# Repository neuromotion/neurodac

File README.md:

# Installation
## Python
The python code relies on the "sounddevice" package. Install this using:
'''pip install sounddevice"
## MATLAB
The MATLAB code relies on the Audio Systems Toolbox. To install it go to the add-on manager in MATLAB IDE,
search for this toolbox and install it. This is not a standard toolbox so you may need to check with your
insitution to make sure you have access to it (I had to get Brown to purchase it). If you cannot get access 
the Python code works just as well.
# Description of files
## eagle-schematic/
Contains the eagle schematics for the NeuroDAC signal conditioning PCB.
## MATLAB/
Contains example code for using NeuroDAC with MATLAB
### playSine.m
This is a script to play 30 seconds of a sine wave a different frequencies on each channel.
This is helpful for testing the system and making sure that you have all the software installed properly.
### playDAC.m
A function for playing a vector of data using a single channel of NeuroDAC
### playDACSimul.m
A function for playing 8 channels of data out of NeuroDAC simultaneously
## Python/
Contains example code for using the NeuroDAC with Python
### playSine.py
This is a Python file that works similarly to the MATLAB_Sine script described above. It plays 8 sine waves each at 10 Hz out of all channels of the NeuroDAC. Use this to test your system.

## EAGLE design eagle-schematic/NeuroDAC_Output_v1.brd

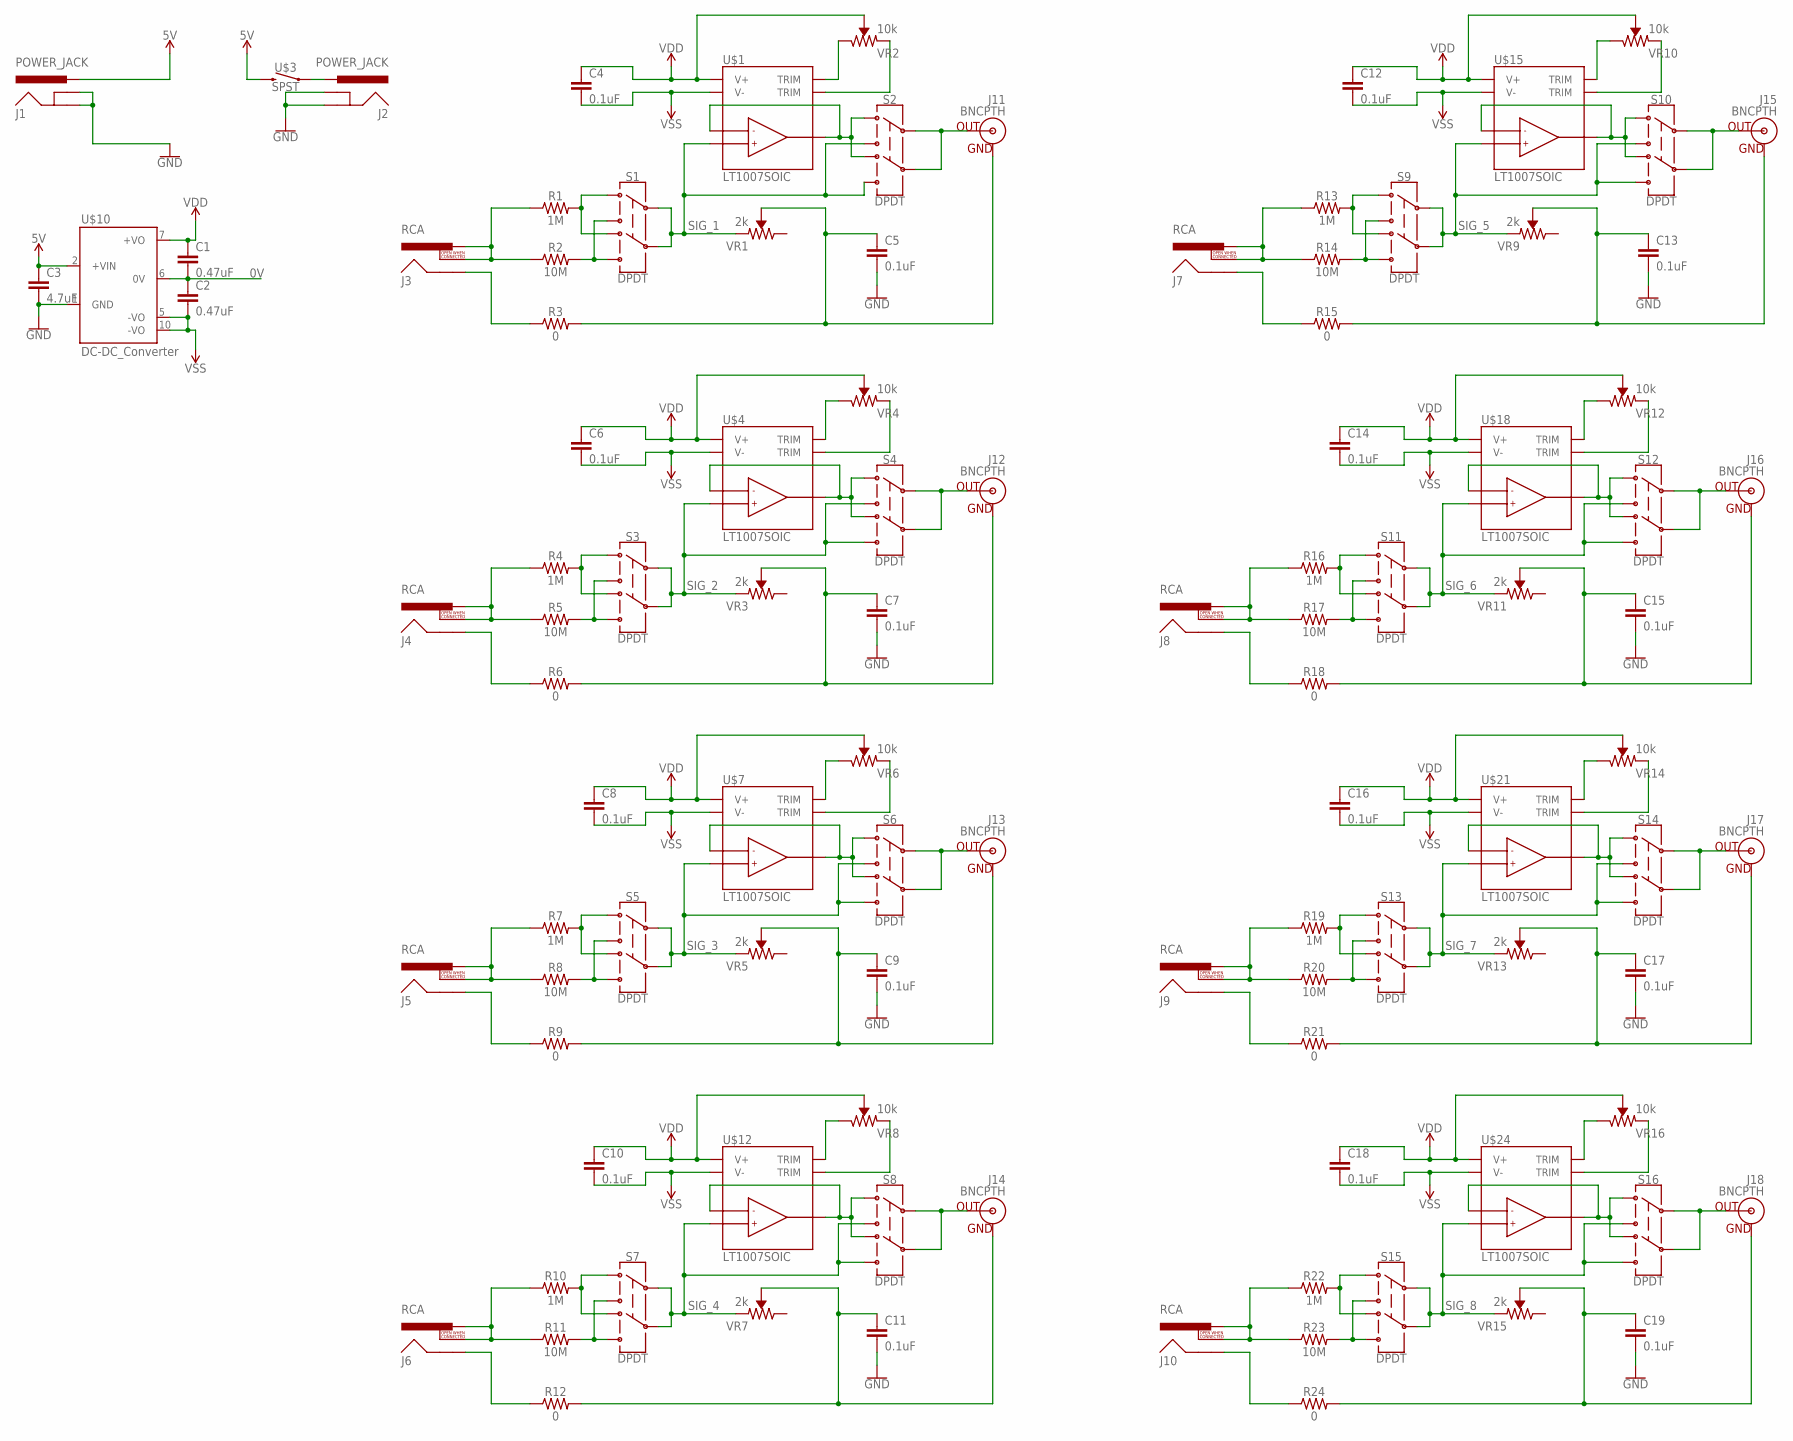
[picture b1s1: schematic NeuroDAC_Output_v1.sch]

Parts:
C1, C2: 0.47uF; 0603
C3: 4.7uF; 0805
C4, C5, C6, C7, C8, C9, C10, C11, C12, C13, C14, C15, C16, C17, C18, C19: 0.1uF; 0603
J1, J2: POWER_JACK; POWER_JACK_PTH
J3, J4, J5, J6, J7, J8, J9, J10: RCA; RCA_LARGE_HOLE
J11, J12, J13, J14, J15, J16, J17, J18: BNCPTH; BNC
R1, R4, R7, R10, R13, R16, R19, R22: 1M; 0603
R2, R5, R8, R11, R14, R17, R20, R23: 10M; 0603
R3, R6, R9, R12, R15, R18, R21, R24: 0; 0603
S1, S2, S3, S4, S5, S6, S7, S8, S9, S10, S11, S12, S13, S14, S15, S16: DPDT; SWITCH_DPDT_JS202011SCQN
U$1, U$4, U$7, U$12, U$15, U$18, U$21, U$24: LT1007SOIC; S8
U$3: SPST; SWITCH_SPST_L101011MS02Q
U$10: DC-DC_Converter; VAT2-SMT
VR1, VR3, VR5, VR7, VR9, VR11, VR13, VR15: 2k; TRIMPOT-SMD-ST4EB
VR2, VR4, VR6, VR8, VR10, VR12, VR14, VR16: 10k; TRIMPOT-SMD-ST4EB

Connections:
0V: C1.2, C2.1, C5.1, C7.1, C9.1, C11.1, C13.1, C15.1, C17.1, C19.1, J11.GND, J12.GND, J13.GND, J14.GND, J15.GND, J16.GND, J17.GND, J18.GND, R3.2, R6.2, R9.2, R12.2, R15.2, R18.2, R21.2, R24.2, U$10.6 (0V), VR1.2 (WIPER), VR3.2 (WIPER), VR5.2 (WIPER), VR7.2 (WIPER), VR9.2 (WIPER), VR11.2 (WIPER), VR13.2 (WIPER), VR15.2 (WIPER)
5V: C3.1, J1.PWR, U$3.2, U$10.2 (+VIN)
GND: C3.2, C5.2, C7.2, C9.2, C11.2, C13.2, C15.2, C17.2, C19.2, J1.GND, J1.GNDBREAK, J2.GND, J2.GNDBREAK, U$10.1 (GND)
unnamed: J3.PIN, J3.SWITCH, R1.1, R2.1
unnamed: R1.2, S1.1, S1.4
unnamed: J2.PWR, U$3.1
unnamed: R2.2, S1.3, S1.6
unnamed: R4.2, S3.1, S3.4
unnamed: J3.SHELL, R3.1
unnamed: U$1.1 (TRIM), VR2.3 (CW)
unnamed: S2.1, S2.4, U$1.2 (IN-), U$1.6 (OUT)
unnamed: U$1.8 (TRIM), VR2.1 (CCW)
unnamed: J4.PIN, J4.SWITCH, R4.1, R5.1
unnamed: R5.2, S3.3, S3.6
unnamed: R7.2, S5.1, S5.4
unnamed: R8.2, S5.3, S5.6
unnamed: J4.SHELL, R6.1
unnamed: S4.1, S4.4, U$4.2 (IN-), U$4.6 (OUT)
unnamed: U$4.1 (TRIM), VR4.3 (CW)
unnamed: U$4.8 (TRIM), VR4.1 (CCW)
unnamed: J5.PIN, J5.SWITCH, R7.1, R8.1
unnamed: R10.2, S7.1, S7.4
unnamed: R11.2, S7.3, S7.6
unnamed: R13.2, S9.1, S9.4
unnamed: J5.SHELL, R9.1
unnamed: S6.1, S6.4, U$7.2 (IN-), U$7.6 (OUT)
unnamed: U$7.1 (TRIM), VR6.3 (CW)
unnamed: U$7.8 (TRIM), VR6.1 (CCW)
unnamed: J6.PIN, J6.SWITCH, R10.1, R11.1
unnamed: R14.2, S9.3, S9.6
unnamed: R16.2, S11.1, S11.4
unnamed: R17.2, S11.3, S11.6
unnamed: J6.SHELL, R12.1
unnamed: S8.1, S8.4, U$12.2 (IN-), U$12.6 (OUT)
unnamed: U$12.1 (TRIM), VR8.3 (CW)
unnamed: U$12.8 (TRIM), VR8.1 (CCW)
unnamed: J7.PIN, J7.SWITCH, R13.1, R14.1
unnamed: R19.2, S13.1, S13.4
unnamed: R20.2, S13.3, S13.6
unnamed: R22.2, S15.1, S15.4
unnamed: J7.SHELL, R15.1
unnamed: S10.1, S10.4, U$15.2 (IN-), U$15.6 (OUT)
unnamed: U$24.1 (TRIM), VR16.3 (CW)
unnamed: U$15.8 (TRIM), VR10.1 (CCW)
unnamed: J8.PIN, J8.SWITCH, R16.1, R17.1
unnamed: R23.2, S15.3, S15.6
unnamed: J11.S (OUT), S2.2, S2.5
unnamed: J12.S (OUT), S4.2, S4.5
unnamed: J8.SHELL, R18.1
unnamed: S12.1, S12.4, U$18.2 (IN-), U$18.6 (OUT)
unnamed: U$21.1 (TRIM), VR14.3 (CW)
unnamed: U$18.8 (TRIM), VR12.1 (CCW)
unnamed: J9.PIN, J9.SWITCH, R19.1, R20.1
unnamed: J13.S (OUT), S6.2, S6.5
unnamed: J14.S (OUT), S8.2, S8.5
unnamed: J15.S (OUT), S10.2, S10.5
unnamed: J9.SHELL, R21.1
unnamed: S14.1, S14.4, U$21.2 (IN-), U$21.6 (OUT)
unnamed: U$18.1 (TRIM), VR12.3 (CW)
unnamed: U$21.8 (TRIM), VR14.1 (CCW)
unnamed: J10.PIN, J10.SWITCH, R22.1, R23.1
unnamed: J16.S (OUT), S12.2, S12.5
unnamed: J17.S (OUT), S14.2, S14.5
unnamed: J18.S (OUT), S16.2, S16.5
unnamed: J10.SHELL, R24.1
unnamed: S16.1, S16.4, U$24.2 (IN-), U$24.6 (OUT)
unnamed: U$15.1 (TRIM), VR10.3 (CW)
unnamed: U$24.8 (TRIM), VR16.1 (CCW)
SIG_1: S1.2, S1.5, S2.3, S2.6, U$1.3 (IN+), VR1.1 (CCW)
SIG_2: S3.2, S3.5, S4.3, S4.6, U$4.3 (IN+), VR3.1 (CCW)
SIG_3: S5.2, S5.5, S6.3, S6.6, U$7.3 (IN+), VR5.1 (CCW)
SIG_4: S7.2, S7.5, S8.3, S8.6, U$12.3 (IN+), VR7.1 (CCW)
SIG_5: S9.2, S9.5, S10.3, S10.6, U$15.3 (IN+), VR9.1 (CCW)
SIG_6: S11.2, S11.5, S12.3, S12.6, U$18.3 (IN+), VR11.1 (CCW)
SIG_7: S13.2, S13.5, S14.3, S14.6, U$21.3 (IN+), VR13.1 (CCW)
SIG_8: S15.2, S15.5, S16.3, S16.6, U$24.3 (IN+), VR15.1 (CCW)
VDD: C1.1, C4.1, C6.1, C8.1, C10.1, C12.1, C14.1, C16.1, C18.1, U$1.7 (V+), U$4.7 (V+), U$7.7 (V+), U$10.7 (+VO), U$12.7 (V+), U$15.7 (V+), U$18.7 (V+), U$21.7 (V+), U$24.7 (V+), VR2.2 (WIPER), VR4.2 (WIPER), VR6.2 (WIPER), VR8.2 (WIPER), VR10.2 (WIPER), VR12.2 (WIPER), VR14.2 (WIPER), VR16.2 (WIPER)
VSS: C2.2, C4.2, C6.2, C8.2, C10.2, C12.2, C14.2, C16.2, C18.2, U$1.4 (V-), U$4.4 (V-), U$7.4 (V-), U$10.5 (-VO), U$10.10 (-VO), U$12.4 (V-), U$15.4 (V-), U$18.4 (V-), U$21.4 (V-), U$24.4 (V-)

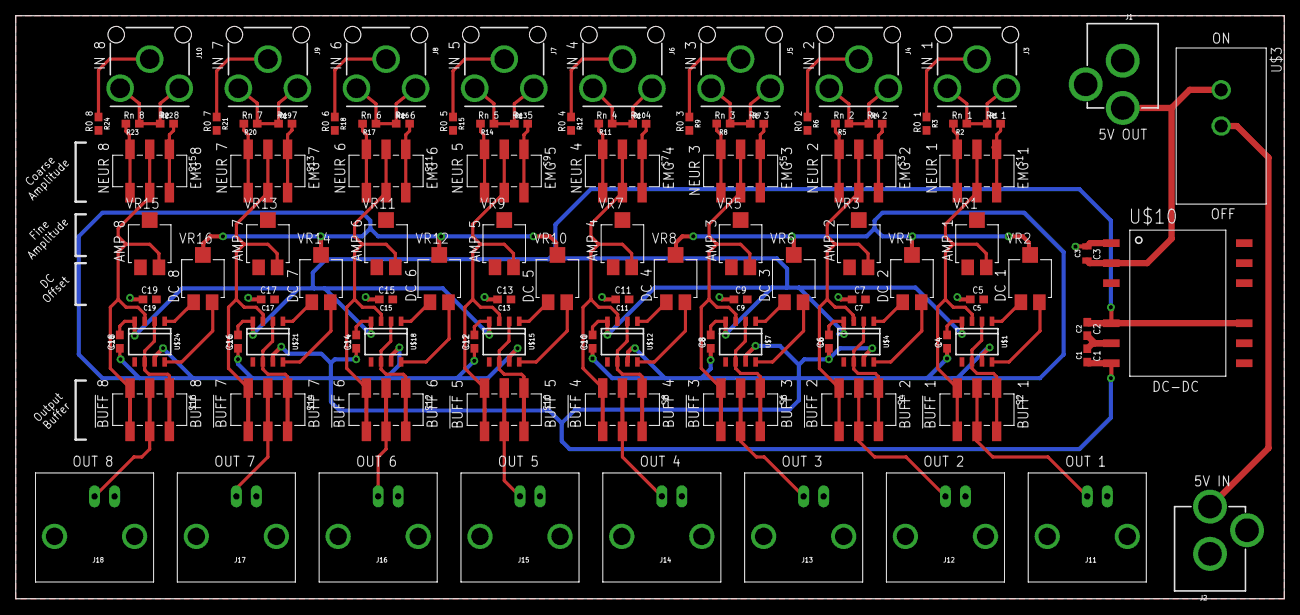
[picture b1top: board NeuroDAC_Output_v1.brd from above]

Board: 2 copper layers, 161.0 x 74.0 mm, 103 parts (0 on the bottom side), 78 nets.

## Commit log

2019-11-06 Initial commit, ignoring Starbuck data
2019-11-08 Changed sample rate to 48000 to match MCHStreamer device
2019-11-08 Organized repo and added README.md
2020-10-02 Updated source files, added schematics
2020-10-02 Removed unnessary files
2020-10-02 Renaming files
2020-10-02 Create LICENSE
2020-10-06 Update README.md
    Added DOI mark.

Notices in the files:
parts and their libraries:
SparkFun-Capacitors: Licensing: Creative Commons ShareAlike 4.0 International - https://creativecommons.org/licenses/by-sa/4.0
